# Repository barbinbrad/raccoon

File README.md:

# Raccoon
PCB and firmware for a USB to CAN interface, with support for 4 CAN transceivers and an optional NEO-MP8 GNSS module. The design is a reverse-engineering of comma.ai's Black Panda. It uses a modified version of the [panda](https://github.com/commaai/panda) firmware/SDK.

## Usage
For self-driving, it is better to buy a [red panda](https://comma.ai/shop/products/panda) from comma.ai. In addition to getting a more reliable product, you'll be supporting open-source software and a really smart group of people.

## Header

The design uses an automotive-grade Deutsch header, which eliminates the need for a switching relay. Feel free to replace this with something else. If you want to use ["ODB-C"](https://github.com/commaai/neo/blob/master/car_harness/OBD-C.sch.pdf) you'll need to use pins C0/C3 (inputs), C10/C11 (outputs). 

To use the deutsch header, you'll need a [crimper](https://www.buydeutsch.com/collections/crimpers/products/18890) and some parts:

- 1 [DTM13-12A](https://www.alliedelec.com/product/te-connectivity/dtm13-12pa/70979342/) or some variant of the header. This needs hand-soldered.
- 1 [DTM06-12S](https://www.buydeutsch.com/collections/dtm-series/products/dtm06-12sa), the male connector
- 1 [WM-12S](https://www.buydeutsch.com/collections/dtm-series/products/wm-12s), a wedgelock
- 12 [Crimpable Sockets](https://www.buydeutsch.com/products/0462-201-20141)

## Hand-Soldered Components
There are a few components that need purchased and hand-soldered to make the board work.
- 1 [USB-B Connector](https://www.digikey.com/en/products/detail/molex,-llc/0670688000/773801)
- 2 [Push Button Switches](https://www.mouser.com/ProductDetail/Grayhill/95C06C3RAT)

## GPS
If you order the board as-is from JLCPCB, you can use it with or without GPS. 

To use it with GPS, you'll need to hand-solder/install these parts:

- 1 [NEO-MP8-2](https://www.digikey.com/en/products/detail/u-blox/NEO-M8P-2/6150645)
- 1 [W2H15C4738AT1A](https://www.digikey.com/en/products/detail/avx-corporation/W2H15C4738AT1A/2004490), a feedthrough capacitor for the GPS antenna. 
- 1 Active GNSS Antenna. See [Table 7](https://www.u-blox.com/sites/default/files/NEO-8Q-NEO-M8-FW3_HIM_UBX-15029985.pdf) in the NEO-M8P guide for recommendations. 

To use it without GPS, just jump the through-holes labeled NO_GPS. This will tell the firmware to ignore the GPS.

## Warning
The board design is untested because of the chip shortage. Use at your own risk.

## Credit
Credit to [mickabrig7](https://github.com/mickabrig7/raccoon) for the original design and his guidance.

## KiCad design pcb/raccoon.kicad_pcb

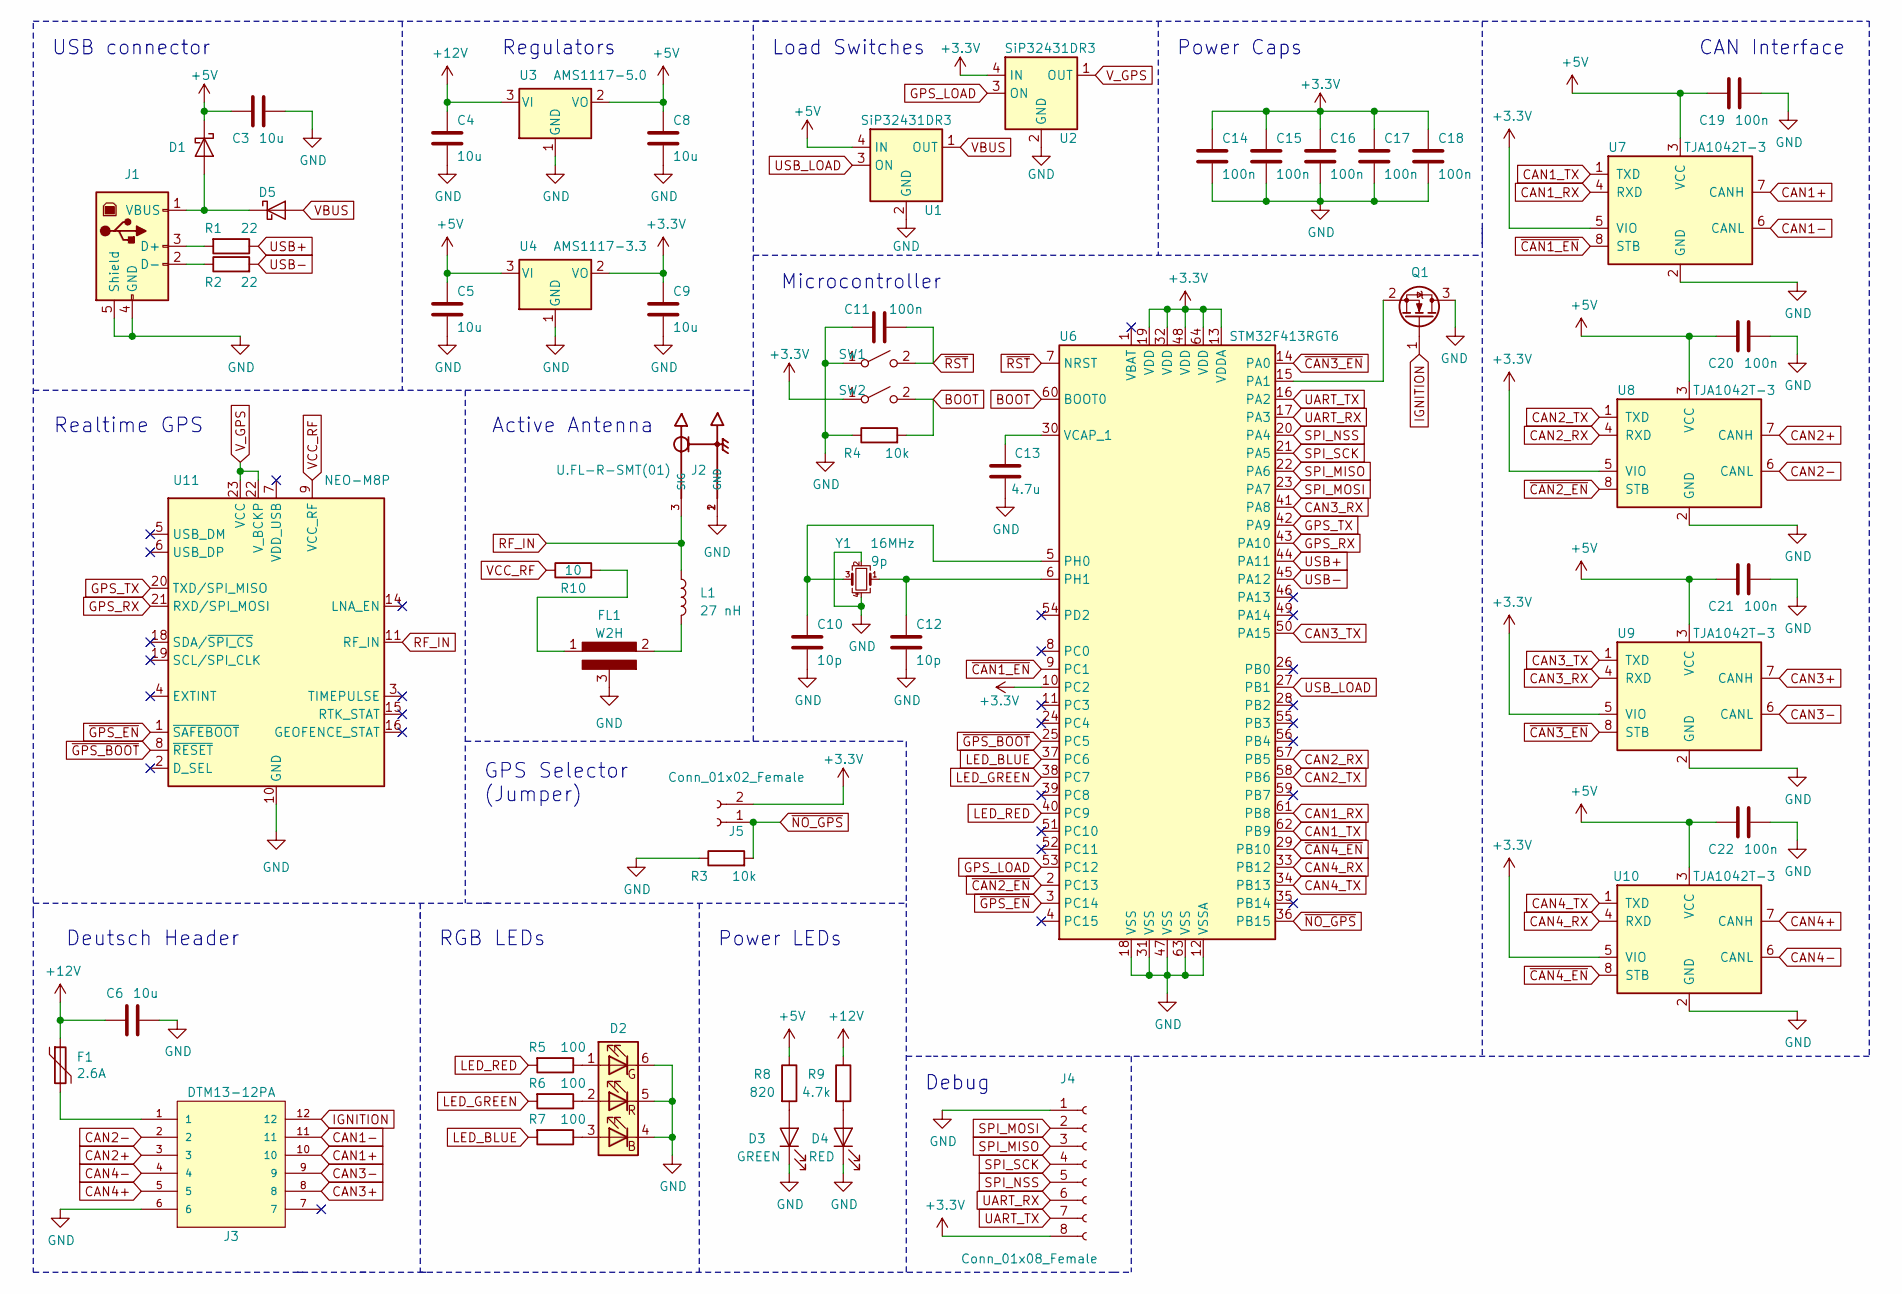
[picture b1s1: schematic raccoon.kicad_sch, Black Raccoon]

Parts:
C3, C4, C5, C6, C8, C9: 10u; C_0805_2012Metric; LCSC C15850
C10, C12: 10p; C_0402_1005Metric; LCSC C32949
C11, C14, C15, C16, C17, C18, C19, C20, C21, C22: 100n; C_0603_1608Metric; LCSC C14663
C13: 4.7u; C_0603_1608Metric; LCSC C19666
D1, D5: D_Schottky; D_SMA; LCSC C8678
D2: LED_RGB; LED_RGB_5050-6; LCSC C409780
D3: GREEN; LED_0603_1608Metric; LCSC C72043
D4: RED; LED_0603_1608Metric; LCSC C2286
F1: 2.6A; Fuse_1812_4532Metric; LCSC C207183
FL1: W2H; W2H15C4738AT1A
J1: USB_B; USB_B_OST_USB-B1HSxx_Horizontal
J2: U.FL-R-SMT(01); HRS_U.FL-R-SMT(01); LCSC C88373
J3: DTM13-12PA; TE_DTM13-12PA
J4: Conn_01x08_Female; PinHeader_1x08_P2.54mm_Vertical
J5: Conn_01x02_Female; PinHeader_1x02_P2.54mm_Vertical
L1: 27 nH; L_0603_1608Metric; LCSC C12100
Q1: Q_NMOS_GSD; SOT-23; LCSC C8545
R1, R2: 22; R_0603_1608Metric; LCSC C23345
R3, R4: 10k; R_0603_1608Metric; LCSC C25804
R5, R6, R7: 100; R_0603_1608Metric; LCSC C22775
R8: 820; R_0603_1608Metric; LCSC C23253
R9: 4.7k; R_0603_1608Metric; LCSC C23162
R10: 10; R_0402_1005Metric; LCSC C25077
SW1, SW2: SW_SPST; SW_PUSH_6mm_H8mm
U1, U2: SiP32431DR3; SOT-363_SC-70-6; LCSC C141606
U3: AMS1117-5.0; SOT-223-3_TabPin2; LCSC C6187
U4: AMS1117-3.3; SOT-223-3_TabPin2; LCSC C6186
U6: STM32F413RGT6; LQFP-64_10x10mm_P0.5mm; LCSC C468260
U7, U8, U9, U10: TJA1042T-3; SOIC-8_3.9x4.9mm_P1.27mm; LCSC C132227
U11: NEO-M8P; ublox_NEO
Y1: 16MHz; Crystal_SMD_3225-4Pin_3.2x2.5mm; LCSC C13738

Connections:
+3V3: C9.1, C14.1, C15.1, C16.1, C17.1, C18.1, J4.8, J5.2, SW2.1 (A), U2.4 (IN), U4.2 (VO), U6.10 (PC2), U6.13 (VDDA), U6.19 (VDD), U6.32 (VDD), U6.48 (VDD), U6.64 (VDD), U7.5 (VIO), U8.5 (VIO), U9.5 (VIO), U10.5 (VIO)
+5V: C3.2, C5.1, C8.1, C19.2, C20.2, C21.2, C22.2, D1.1 (K), R8.1, U1.4 (IN), U3.2 (VO), U4.3 (VI), U7.3 (VCC), U8.3 (VCC), U9.3 (VCC), U10.3 (VCC)
+12V: C4.1, C6.2, F1.1, R9.1, U3.3 (VI)
BOOT: R4.2, SW2.2 (B), U6.60 (BOOT0)
CAN1+: J3.10, U7.7 (CANH)
CAN1-: J3.11, U7.6 (CANL)
CAN1_RX: U6.61 (PB8), U7.4 (RXD)
CAN1_TX: U6.62 (PB9), U7.1 (TXD)
CAN2+: J3.3, U8.7 (CANH)
CAN2-: J3.2, U8.6 (CANL)
CAN2_RX: U6.57 (PB5), U8.4 (RXD)
CAN2_TX: U6.58 (PB6), U8.1 (TXD)
CAN3+: J3.8, U9.7 (CANH)
CAN3-: J3.9, U9.6 (CANL)
CAN3_RX: U6.41 (PA8), U9.4 (RXD)
CAN3_TX: U6.50 (PA15), U9.1 (TXD)
CAN4+: J3.5, U10.7 (CANH)
CAN4-: J3.4, U10.6 (CANL)
CAN4_RX: U6.33 (PB12), U10.4 (RXD)
CAN4_TX: U6.34 (PB13), U10.1 (TXD)
GND: C3.1, C4.2, C5.2, C6.1, C8.2, C9.2, C10.2, C11.2, C12.2, C13.1, C14.2, C15.2, C16.2, C17.2, C18.2, C19.1, C20.1, C21.1, C22.1, D2.4 (BK), D2.5 (GK), D2.6 (RK), D3.1 (K), D4.1 (K), FL1.3, J1.4 (GND), J1.5 (Shield), J2.1 (GND), J2.2 (GND), J3.6, J4.1, Q1.3 (D), R3.1, R4.1, SW1.1 (A), U1.2 (GND), U1.5 (GND), U2.2 (GND), U2.5 (GND), U3.1 (GND), U4.1 (GND), U6.12 (VSSA), U6.18 (VSS), U6.31 (VSS), U6.47 (VSS), U6.63 (VSS), U7.2 (GND), U8.2 (GND), U9.2 (GND), U10.2 (GND), U11.10 (GND), U11.12 (GND), U11.13 (GND), U11.24 (GND), Y1.2, Y1.4
GPS_LOAD: U2.3 (ON), U6.53 (PC12)
GPS_RX: U6.43 (PA10), U11.21 (RXD/SPI_MOSI)
GPS_TX: U6.42 (PA9), U11.20 (TXD/SPI_MISO)
IGNITION: J3.12, Q1.1 (G)
LED_BLUE: R7.2, U6.37 (PC6)
LED_GREEN: R6.2, U6.38 (PC7)
LED_RED: R5.2, U6.40 (PC9)
unnamed: C10.1, U6.5 (PH0), Y1.3
unnamed: C12.1, U6.6 (PH1), Y1.1
unnamed: C13.2, U6.30 (VCAP_1)
unnamed: D1.2 (A), D5.1 (K), J1.1 (VBUS)
unnamed: D2.1 (RA), R5.1
unnamed: D2.2 (GA), R6.1
unnamed: D2.3 (BA), R7.1
unnamed: D3.2 (A), R8.2
unnamed: D4.2 (A), R9.2
unnamed: F1.2, J3.1
unnamed: FL1.1, R10.2
unnamed: FL1.2, L1.2
unnamed: J1.2 (D-), R2.1
unnamed: J1.3 (D+), R1.2
unnamed: Q1.2 (S), U6.15 (PA1)
RF_IN: J2.3 (SIG), L1.1, U11.11 (RF_IN)
SPI_MISO: J4.3, U6.22 (PA6)
SPI_MOSI: J4.2, U6.23 (PA7)
SPI_NSS: J4.5, U6.20 (PA4)
SPI_SCK: J4.4, U6.21 (PA5)
UART_RX: J4.6, U6.17 (PA3)
UART_TX: J4.7, U6.16 (PA2)
USB+: R1.1, U6.44 (PA11)
USB-: R2.2, U6.45 (PA12)
USB_LOAD: U1.3 (ON), U6.27 (PB1)
VBUS: D5.2 (A), U1.1 (OUT)
VCC_RF: R10.1, U11.9 (VCC_RF)
V_GPS: U2.1 (OUT), U11.22 (V_BCKP), U11.23 (VCC)
~CAN1_EN~: U6.9 (PC1), U7.8 (STB)
~CAN2_EN~: U6.2 (PC13), U8.8 (STB)
~CAN3_EN~: U6.14 (PA0), U9.8 (STB)
~CAN4_EN~: U6.29 (PB10), U10.8 (STB)
~GPS_BOOT~: U6.25 (PC5), U11.8 (~RESET)
~GPS_EN~: U6.3 (PC14), U11.1 (~SAFEBOOT)
~NO_GPS~: J5.1, R3.2, U6.36 (PB15)
~RST~: C11.1, SW1.2 (B), U6.7 (NRST)

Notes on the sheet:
USB connector
Realtime GPS
Deutsch Header
GPS Selector (Jumper)
Regulators
RGB LEDs
Active Antenna
Power LEDs
Load Switches
Microcontroller
Debug
Power Caps
CAN Interface

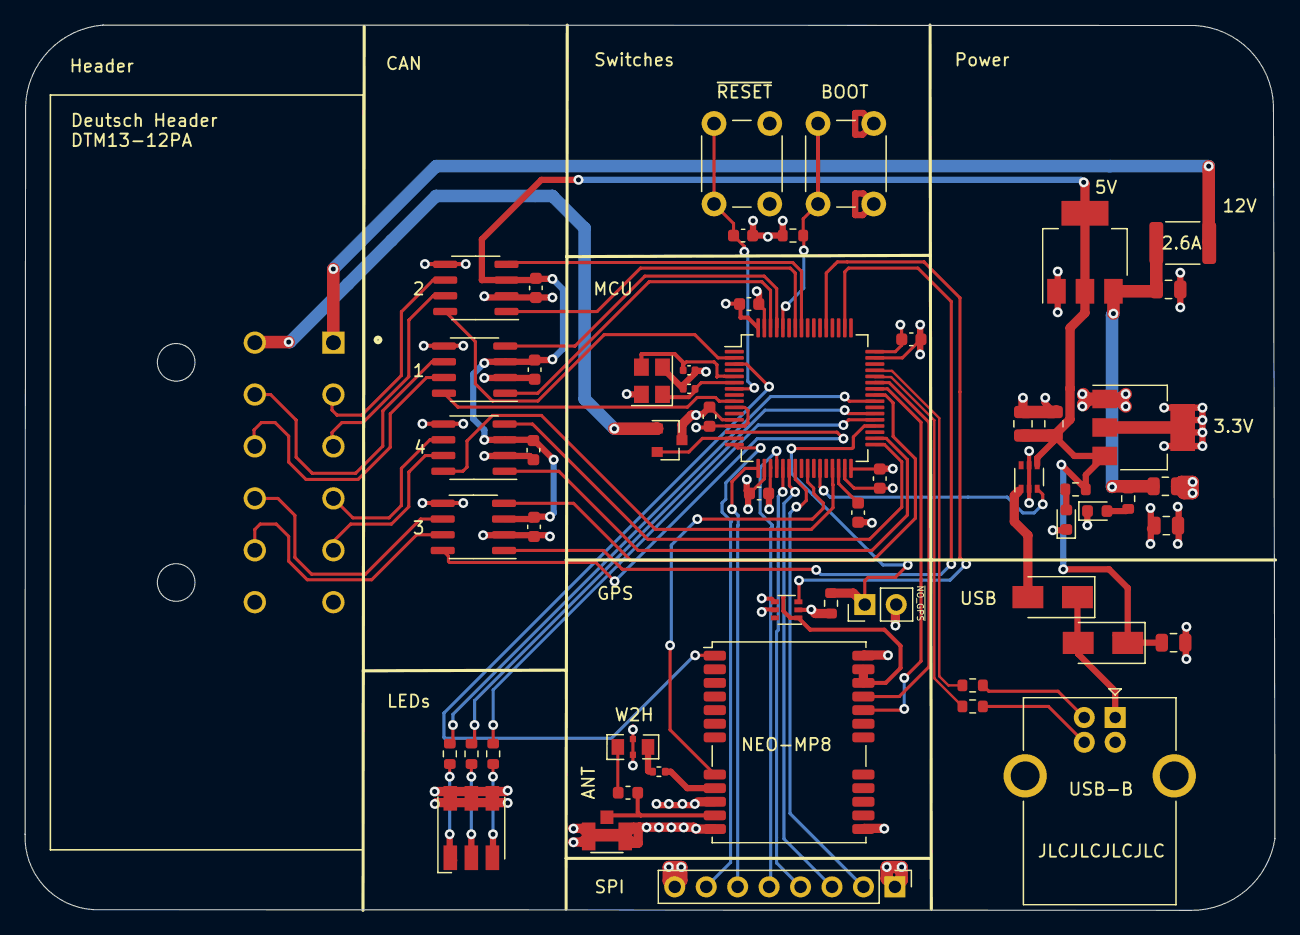
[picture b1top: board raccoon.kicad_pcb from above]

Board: 4 copper layers, 100.9 x 71.5 mm, 56 parts (0 on the bottom side), 64 nets.

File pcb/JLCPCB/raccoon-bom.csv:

Comment,Designator,Footprint,LCSC
"10p","C10,C12","Capacitor_SMD:C_0402_1005Metric","C32949"
"100n","C11,C14,C15,C16,C17,C18,C19,C20,C21,C22","Capacitor_SMD:C_0603_1608Metric","C14663"
"4.7u","C13","Capacitor_SMD:C_0603_1608Metric","C19666"
"10u","C3,C4,C5,C6,C8,C9","Capacitor_SMD:C_0805_2012Metric","C15850"
"D_Schottky","D1,D5","Diode_SMD:D_SMA","C8678"
"LED_RGB","D2","LED_SMD:LED_RGB_5050-6","C409780"
"GREEN","D3","LED_SMD:LED_0603_1608Metric","C72043"
"RED","D4","LED_SMD:LED_0603_1608Metric","C2286"
"2.6A","F1","Fuse:Fuse_1812_4532Metric","C207183"
"W2H","FL1","raccoon:W2H15C4738AT1A",""
"USB_B","J1","Connector_USB:USB_B_OST_USB-B1HSxx_Horizontal",""
"U.FL-R-SMT(01)","J2","kicad-footprints:HRS_U.FL-R-SMT(01)","C88373"
"DTM13-12PA","J3","kicad-footprints:TE_DTM13-12PA",""
"Conn_01x08_Female","J4","Connector_PinHeader_2.54mm:PinHeader_1x08_P2.54mm_Vertical",""
"Conn_01x02_Female","J5","Connector_PinHeader_2.54mm:PinHeader_1x02_P2.54mm_Vertical",""
"27 nH","L1","Inductor_SMD:L_0603_1608Metric","C12100"
"Q_NMOS_GSD","Q1","Package_TO_SOT_SMD:SOT-23","C8545"
"22","R1,R2","Resistor_SMD:R_0603_1608Metric","C23345"
"10","R10","Resistor_SMD:R_0402_1005Metric","C25077"
"10k","R3,R4","Resistor_SMD:R_0603_1608Metric","C25804"
"100","R5,R6,R7","Resistor_SMD:R_0603_1608Metric","C22775"
"820","R8","Resistor_SMD:R_0603_1608Metric","C23253"
"4.7k","R9","Resistor_SMD:R_0603_1608Metric","C23162"
"SW_SPST","SW1,SW2","Button_Switch_THT:SW_PUSH_6mm_H8mm",""
"SiP32431DR3","U1,U2","Package_TO_SOT_SMD:SOT-363_SC-70-6","C141606"
"NEO-M8P","U11","RF_GPS:ublox_NEO",""
"AMS1117-5.0","U3","Package_TO_SOT_SMD:SOT-223-3_TabPin2","C6187"
"AMS1117-3.3","U4","Package_TO_SOT_SMD:SOT-223-3_TabPin2","C6186"
"STM32F413RGT6","U6","Package_QFP:LQFP-64_10x10mm_P0.5mm","C468260"
"TJA1042T-3","U7,U8,U9,U10","Package_SO:SOIC-8_3.9x4.9mm_P1.27mm","C132227"
"16MHz","Y1","Crystal:Crystal_SMD_3225-4Pin_3.2x2.5mm","C13738"

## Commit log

2021-07-02 set GPIOB15 to input
2021-07-03 move button labels
2021-07-05 panda as submodule
2021-07-05 update gitignore
2021-07-05 update panda firmware
